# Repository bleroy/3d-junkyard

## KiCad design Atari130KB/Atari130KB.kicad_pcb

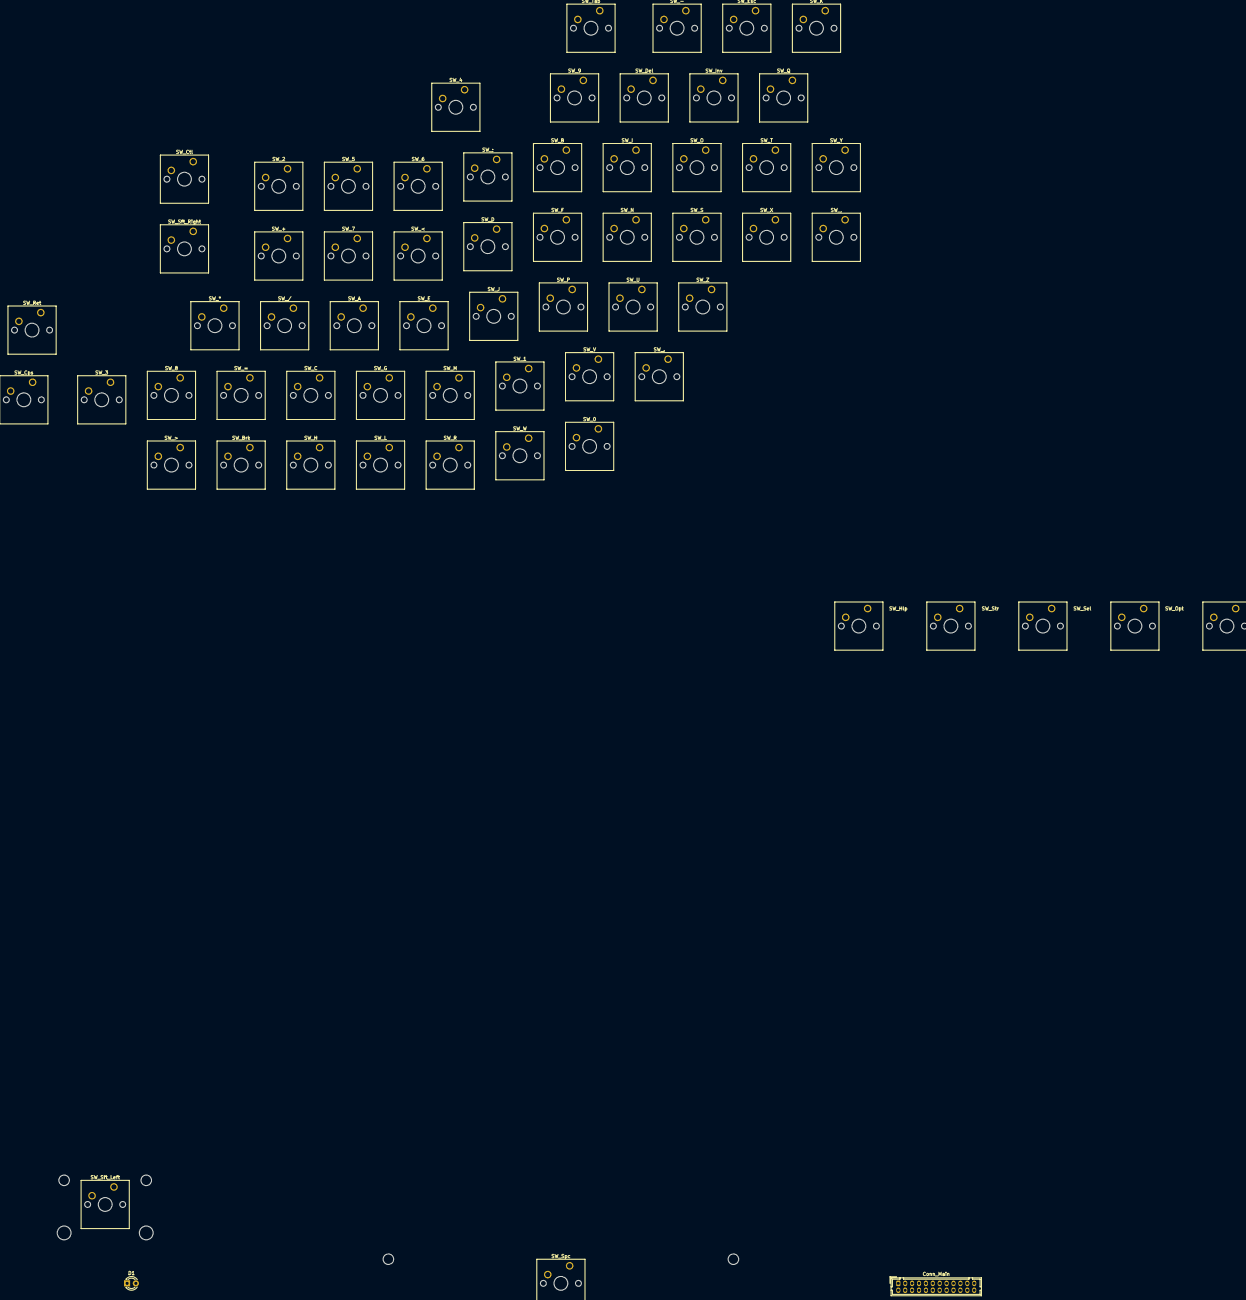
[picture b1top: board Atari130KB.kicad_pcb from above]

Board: 2 copper layers, 64 parts (0 on the bottom side), 15 nets, no tracks yet.

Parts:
Conn_Main: Conn_02x12_Counter_Clockwise_MountingPin; Hirose_DF11-24DP-2DSA_2x12_P2.00mm_Vertical
D1: LED; LED_D3.0mm
SW_0, SW_1, SW_2, SW_3, SW_4, SW_5, SW_6, SW_7, SW_8, SW_9, SW_.: SW_MEC_5G; SW_Cherry_MX_1.00u_PCB
SW_*: SW_MEC_5G; SW_Cherry_MX_1.00u_PCB
SW_+: SW_MEC_5G; SW_Cherry_MX_1.00u_PCB
SW_,: SW_MEC_5G; SW_Cherry_MX_1.00u_PCB
SW_-: SW_MEC_5G; SW_Cherry_MX_1.00u_PCB
SW_/: SW_MEC_5G; SW_Cherry_MX_1.00u_PCB
SW_;: SW_MEC_5G; SW_Cherry_MX_1.00u_PCB
SW_<: SW_MEC_5G; SW_Cherry_MX_1.00u_PCB
SW_=: SW_MEC_5G; SW_Cherry_MX_1.00u_PCB
SW_>: SW_MEC_5G; SW_Cherry_MX_1.00u_PCB
SW_A: SW_MEC_5G; SW_Cherry_MX_1.00u_PCB
SW_B: SW_MEC_5G; SW_Cherry_MX_1.00u_PCB
SW_Brk: SW_MEC_5G; SW_Cherry_MX_1.00u_PCB
SW_C: SW_MEC_5G; SW_Cherry_MX_1.00u_PCB
SW_Cps: SW_MEC_5G; SW_Cherry_MX_1.25u_PCB
SW_Ctl: SW_MEC_5G; SW_Cherry_MX_1.75u_PCB
SW_D: SW_MEC_5G; SW_Cherry_MX_1.00u_PCB
SW_Del: SW_MEC_5G; SW_Cherry_MX_1.00u_PCB
SW_E: SW_MEC_5G; SW_Cherry_MX_1.00u_PCB
SW_Esc: SW_MEC_5G; SW_Cherry_MX_1.00u_PCB
SW_F: SW_MEC_5G; SW_Cherry_MX_1.00u_PCB
SW_G: SW_MEC_5G; SW_Cherry_MX_1.00u_PCB
SW_H: SW_MEC_5G; SW_Cherry_MX_1.00u_PCB
SW_Hlp: SW_MEC_5G; SW_Cherry_MX_1.50u_Atari_Fn_PCB
SW_I: SW_MEC_5G; SW_Cherry_MX_1.00u_PCB
SW_Inv: SW_MEC_5G; SW_Cherry_MX_1.00u_PCB
SW_J: SW_MEC_5G; SW_Cherry_MX_1.00u_PCB
SW_K: SW_MEC_5G; SW_Cherry_MX_1.00u_PCB
SW_L: SW_MEC_5G; SW_Cherry_MX_1.00u_PCB
SW_M: SW_MEC_5G; SW_Cherry_MX_1.00u_PCB
SW_N: SW_MEC_5G; SW_Cherry_MX_1.00u_PCB
SW_O: SW_MEC_5G; SW_Cherry_MX_1.00u_PCB
SW_Opt: SW_MEC_5G; SW_Cherry_MX_1.50u_Atari_Fn_PCB
SW_P: SW_MEC_5G; SW_Cherry_MX_1.00u_PCB
SW_Q: SW_MEC_5G; SW_Cherry_MX_1.00u_PCB
SW_R: SW_MEC_5G; SW_Cherry_MX_1.00u_PCB
SW_Ret: SW_MEC_5G; SW_Cherry_MX_1.50u_PCB
SW_Rst: SW_MEC_5G; SW_Cherry_MX_1.50u_Atari_Fn_PCB
SW_S: SW_MEC_5G; SW_Cherry_MX_1.00u_PCB
SW_Sel: SW_MEC_5G; SW_Cherry_MX_1.50u_Atari_Fn_PCB
SW_Sft_Left: SW_MEC_5G; SW_Cherry_MX_2.25u_PCB
SW_Sft_Right: SW_MEC_5G; SW_Cherry_MX_1.75u_PCB
SW_Spc: SW_MEC_5G; SW_Cherry_MX_6.25u_PCB
SW_Str: SW_MEC_5G; SW_Cherry_MX_1.50u_Atari_Fn_PCB
SW_T: SW_MEC_5G; SW_Cherry_MX_1.00u_PCB
SW_Tab: SW_MEC_5G; SW_Cherry_MX_1.50u_PCB
SW_U: SW_MEC_5G; SW_Cherry_MX_1.00u_PCB
SW_V: SW_MEC_5G; SW_Cherry_MX_1.00u_PCB
SW_W: SW_MEC_5G; SW_Cherry_MX_1.00u_PCB
SW_X: SW_MEC_5G; SW_Cherry_MX_1.00u_PCB
SW_Y: SW_MEC_5G; SW_Cherry_MX_1.00u_PCB
SW_Z: SW_MEC_5G; SW_Cherry_MX_1.00u_PCB

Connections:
unnamed: Conn_Main.2, D1.2
unnamed: Conn_Main.3, D1.1
unnamed: Conn_Main.4, SW_H.1, SW_H.2, SW_Hlp.1, SW_Hlp.2, SW_J.1, SW_J.2, SW_Spc.1, SW_Spc.2
unnamed: Conn_Main.8, SW_5.1, SW_5.2, SW_8.1, SW_8.2, SW_B.1, SW_B.2, SW_G.1, SW_G.2, SW_I.1, SW_I.2, SW_K.1, SW_K.2, SW_M.1, SW_M.2, SW_T.1, SW_T.2
unnamed: Conn_Main.9, SW_4.1, SW_4.2, SW_9.1, SW_9.2, SW_,.1, SW_,.2, SW_F.1, SW_F.2, SW_L.1, SW_L.2, SW_O.1, SW_O.2, SW_R.1, SW_R.2, SW_V.1, SW_V.2
unnamed: Conn_Main.10, SW_0.1, SW_0.2, SW_3.1, SW_3.2, SW_..1, SW_..2, SW_;.1, SW_;.2, SW_C.1, SW_C.2, SW_D.1, SW_D.2, SW_E.1, SW_E.2, SW_P.1, SW_P.2
unnamed: Conn_Main.11, SW_2.1, SW_2.2, SW_+.1, SW_+.2, SW_-.1, SW_-.2, SW_/.1, SW_/.2, SW_<.1, SW_<.2, SW_S.1, SW_S.2, SW_W.1, SW_W.2, SW_X.1, SW_X.2
unnamed: Conn_Main.16, SW_Cps.1, SW_Cps.2, SW_Del.1, SW_Del.2, SW_Esc.1, SW_Esc.2, SW_Ret.1, SW_Ret.2, SW_Tab.1, SW_Tab.2
unnamed: Conn_Main.17, SW_1.1, SW_1.2, SW_*.1, SW_*.2, SW_=.1, SW_=.2, SW_>.1, SW_>.2, SW_A.1, SW_A.2, SW_Inv.1, SW_Inv.2, SW_Q.1, SW_Q.2, SW_Z.1, SW_Z.2
unnamed: Conn_Main.19, SW_6.1, SW_6.2, SW_7.1, SW_7.2, SW_N.1, SW_N.2, SW_U.1, SW_U.2, SW_Y.1, SW_Y.2
unnamed: Conn_Main.20, SW_Brk.1, SW_Brk.2, SW_Ctl.1, SW_Ctl.2, SW_Sft_Left.1, SW_Sft_Left.2, SW_Sft_Right.1, SW_Sft_Right.2
unnamed: Conn_Main.21, SW_Str.1, SW_Str.2
unnamed: Conn_Main.22, SW_Sel.1, SW_Sel.2
unnamed: Conn_Main.23, SW_Opt.1, SW_Opt.2
unnamed: Conn_Main.24, SW_Rst.1, SW_Rst.2

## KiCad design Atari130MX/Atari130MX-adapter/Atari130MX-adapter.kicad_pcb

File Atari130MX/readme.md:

This page moved [here](../DecentXE/readme.md).

All old versions of the files have been kept in place in order to avoid breaking links, but the newer versions in the DecentXE directory should now be used.

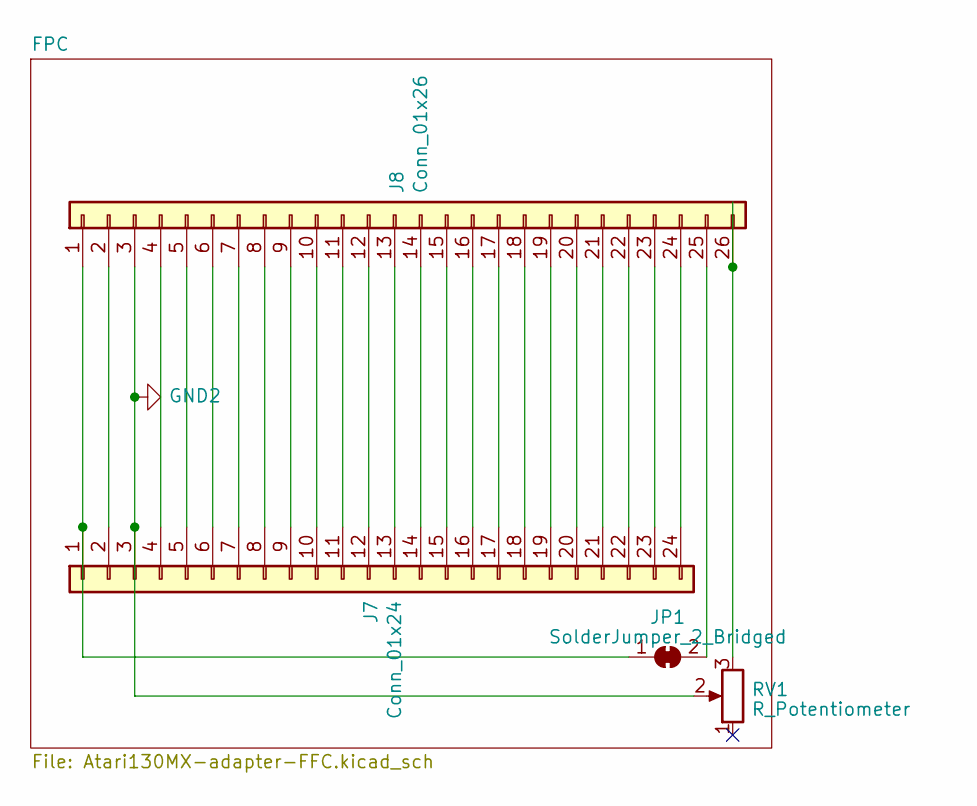
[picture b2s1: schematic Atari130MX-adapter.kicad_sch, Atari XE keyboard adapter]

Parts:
J7: Conn_01x24; 1x24_P1.27mm_Edge_Back
J8: Conn_01x26; Molex_200528-0260_1x26-1MP_P1.00mm_Horizontal
JP1: SolderJumper_2_Bridged; SolderJumper-2_P1.3mm_Bridged_RoundedPad1.0x1.5mm
RV1: R_Potentiometer; Potentiometer_CUI-PTN06-D02CB20

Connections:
GND2: J7.3, J8.3, RV1.2
unnamed: J7.1, J8.1, JP1.1 (A)
unnamed: J7.2, J8.2
unnamed: J7.4, J8.4
unnamed: J7.5, J8.5
unnamed: J7.6, J8.6
unnamed: J7.7, J8.7
unnamed: J7.8, J8.8
unnamed: J7.9, J8.9
unnamed: J7.10, J8.10
unnamed: J7.11, J8.11
unnamed: J7.12, J8.12
unnamed: J7.13, J8.13
unnamed: J7.14, J8.14
unnamed: J7.15, J8.15
unnamed: J7.16, J8.16
unnamed: J7.17, J8.17
unnamed: J7.18, J8.18
unnamed: J7.19, J8.19
unnamed: J7.20, J8.20
unnamed: J7.21, J8.21
unnamed: J7.22, J8.22
unnamed: J7.23, J8.23
unnamed: J7.24, J8.24
unnamed: J8.25, JP1.2 (B)
unnamed: J8.26, RV1.3

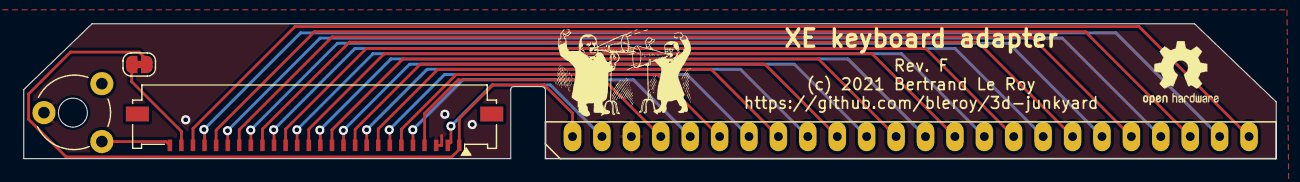
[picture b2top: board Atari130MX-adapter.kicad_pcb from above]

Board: 2 copper layers, 108.1 x 11.6 mm, 4 parts (0 on the bottom side), 26 nets.

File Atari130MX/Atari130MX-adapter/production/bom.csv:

Designator,Footprint,Quantity,Value,LCSC Part #
J1,FPC 1x24 P2.54mm Edge,1,Conn_01x24,
J2,FPC Molex 1x26 P1mm Edge,1,Conn_01x26,

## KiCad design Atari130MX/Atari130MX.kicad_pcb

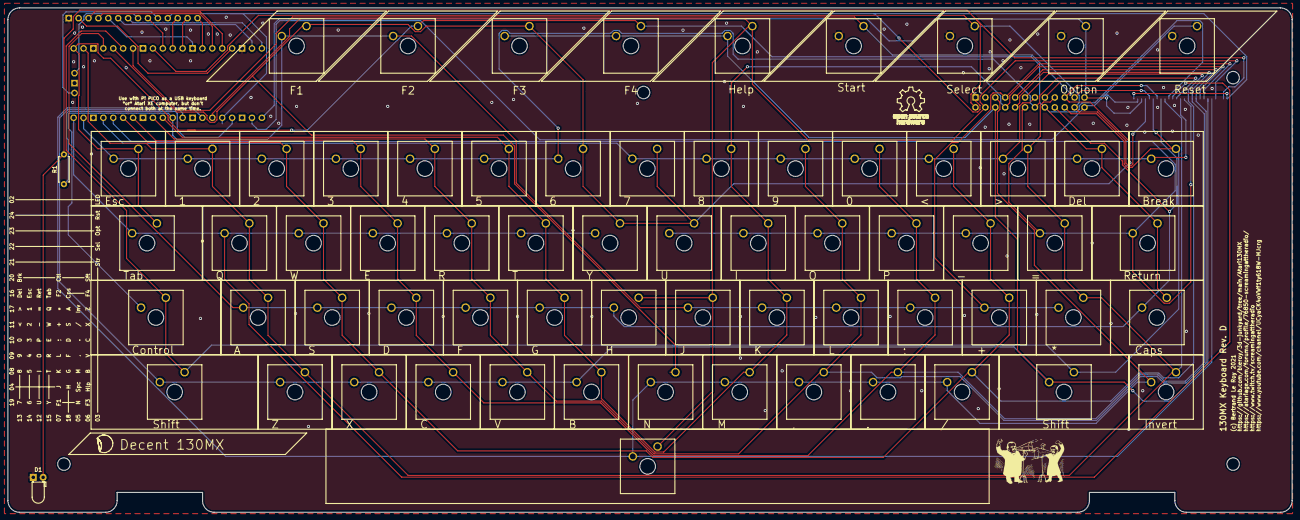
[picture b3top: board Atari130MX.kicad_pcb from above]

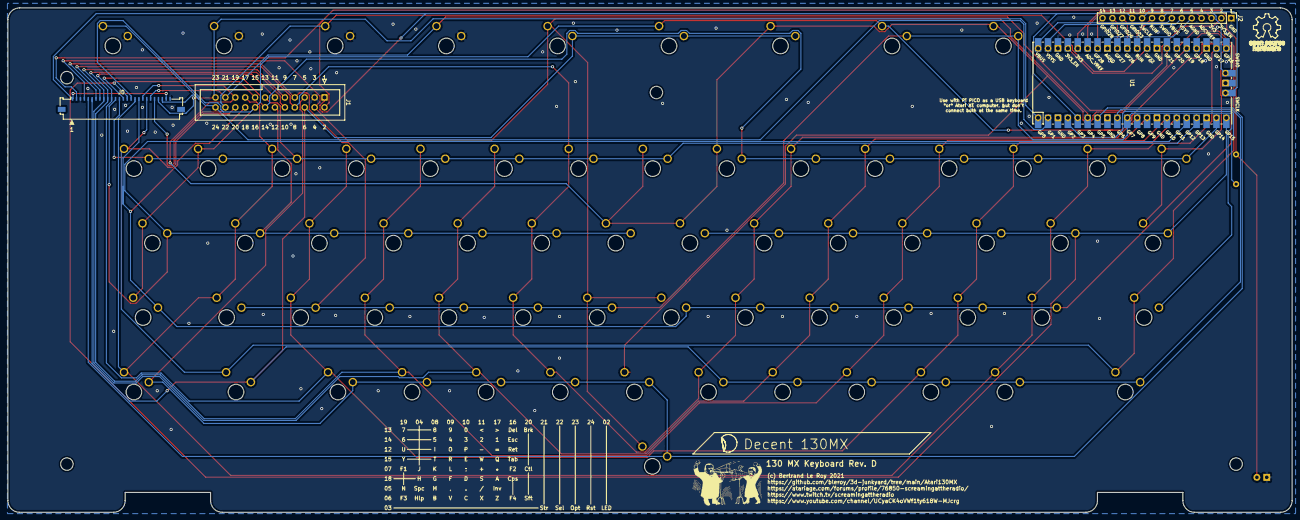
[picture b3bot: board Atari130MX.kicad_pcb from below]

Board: 2 copper layers, 329.2 x 129.3 mm, 76 parts (4 on the bottom side), 37 nets.

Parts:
D1: LED; LED_D3.0mm_Horizontal_O1.27mm_Z2.0mm
J0: Conn_01x26; Molex_200528-0260_1x26-1MP_P1.00mm_Horizontal
J1: Conn_02x12_Odd_Even; IDC-Header_2x12_P2.54mm_Vertical
J2: Conn_01x14; PinHeader_1x14_P2.54mm_Vertical
R1: R100; R_Axial_DIN0207_L6.3mm_D2.5mm_P7.62mm_Horizontal
REF0, REF01, REF02, REF03: MountingHole_3.2mm_M3
SW0, SW1, SW2, SW3, SW4, SW5, SW6, SW7, SW8, SW9: SW_Push_45deg; SW_Kailh_1.00u_PCB
SWA1: SW_Push_45deg; SW_Kailh_1.00u_PCB
SWB1: SW_Push_45deg; SW_Kailh_1.00u_PCB
SWBrk1: SW_Push_45deg; SW_Kailh_1.00u_PCB
SWC1: SW_Push_45deg; SW_Kailh_1.00u_PCB
SWComma1: SW_Push_45deg; SW_Kailh_1.00u_PCB
SWCps1: SW_Push_45deg; SW_Kailh_1.25u_PCB
SWCtl1: SW_Push_45deg; SW_Kailh_1.75u_PCB
SWD1: SW_Push_45deg; SW_Kailh_1.00u_PCB
SWDash1: SW_Push_45deg; SW_Kailh_1.00u_PCB
SWDel1: SW_Push_45deg; SW_Kailh_1.00u_PCB
SWE1: SW_Push_45deg; SW_Kailh_1.00u_PCB
SWEqual1: SW_Push_45deg; SW_Kailh_1.00u_PCB
SWEsc1: SW_Push_45deg; SW_Kailh_1.00u_PCB
SWF1: SW_Push_45deg; SW_Kailh_1.00u_PCB
SWFn1, SWFn2, SWFn3, SWFn4: SW_Push_45deg; SW_Kailh_1.50u_Atari_Fn_PCB
SWG1: SW_Push_45deg; SW_Kailh_1.00u_PCB
SWGT1: SW_Push_45deg; SW_Kailh_1.00u_PCB
SWH1: SW_Push_45deg; SW_Kailh_1.00u_PCB
SWHlp1: SW_Push_45deg; SW_Kailh_1.50u_Atari_Fn_PCB
SWI1: SW_Push_45deg; SW_Kailh_1.00u_PCB
SWInv1: SW_Push_45deg; SW_Kailh_1.00u_PCB
SWJ1: SW_Push_45deg; SW_Kailh_1.00u_PCB
SWK1: SW_Push_45deg; SW_Kailh_1.00u_PCB
SWL1: SW_Push_45deg; SW_Kailh_1.00u_PCB
SWLT1: SW_Push_45deg; SW_Kailh_1.00u_PCB
SWLeftSft1: SW_Push_45deg; SW_Kailh_2.25u_PCB
SWM1: SW_Push_45deg; SW_Kailh_1.00u_PCB
SWN1: SW_Push_45deg; SW_Kailh_1.00u_PCB
SWO1: SW_Push_45deg; SW_Kailh_1.00u_PCB
SWOption1: SW_Push_45deg; SW_Kailh_1.50u_Atari_Fn_PCB
SWP1: SW_Push_45deg; SW_Kailh_1.00u_PCB
SWPeriod1: SW_Push_45deg; SW_Kailh_1.00u_PCB
SWPlus1: SW_Push_45deg; SW_Kailh_1.00u_PCB
SWQ1: SW_Push_45deg; SW_Kailh_1.00u_PCB
SWR1: SW_Push_45deg; SW_Kailh_1.00u_PCB
SWReset1: SW_Push_45deg; SW_Kailh_1.50u_Atari_Fn_PCB
SWRet1: SW_Push_45deg; SW_Kailh_1.50u_PCB
SWRightSft1: SW_Push_45deg; SW_Kailh_1.75u_PCB
SWS1: SW_Push_45deg; SW_Kailh_1.00u_PCB
SWSelect1: SW_Push_45deg; SW_Kailh_1.50u_Atari_Fn_PCB
SWSemi1: SW_Push_45deg; SW_Kailh_1.00u_PCB
SWSlash1: SW_Push_45deg; SW_Kailh_1.00u_PCB
SWSpc1: SW_Push_45deg; SW_Kailh_Atari_Space
SWStar1: SW_Push_45deg; SW_Kailh_1.00u_PCB
SWStart1: SW_Push_45deg; SW_Kailh_1.50u_Atari_Fn_PCB
SWT1: SW_Push_45deg; SW_Kailh_1.00u_PCB
SWTab1: SW_Push_45deg; SW_Kailh_1.50u_PCB
SWU1: SW_Push_45deg; SW_Kailh_1.00u_PCB
SWV1: SW_Push_45deg; SW_Kailh_1.00u_PCB
SWW1: SW_Push_45deg; SW_Kailh_1.00u_PCB
SWX1: SW_Push_45deg; SW_Kailh_1.00u_PCB
SWY1: SW_Push_45deg; SW_Kailh_1.00u_PCB
SWZ1: SW_Push_45deg; SW_Kailh_1.00u_PCB
U1: Pico; RPi_Pico_SMD_TH

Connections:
GND: D1.1, J0.3, J0.26, J1.3, J2.1, SWOption1.2, SWReset1.2, SWSelect1.2, SWStart1.2, U1.38
unnamed: D1.2, J0.2, J1.2, R1.2
unnamed: J0.1, J0.25, J1.1, J2.11, U1.5
unnamed: J0.4, J1.4, SWH1.1, SWHlp1.1, SWJ1.1, SWSpc1.1, U1.6
unnamed: J0.5, J1.5, SWComma1.2, SWInv1.2, SWM1.2, SWN1.2, SWPeriod1.2, SWSlash1.2, SWSpc1.2, U1.7
unnamed: J0.6, J1.6, SWB1.2, SWC1.2, SWFn3.2, SWFn4.2, SWHlp1.2, SWLeftSft1.2, SWRightSft1.2, SWV1.2, SWX1.2, SWZ1.2, U1.9
unnamed: J0.7, J1.7, SWCtl1.2, SWFn1.2, SWFn2.2, SWJ1.2, SWK1.2, SWL1.2, SWPlus1.2, SWSemi1.2, SWStar1.2, U1.10
unnamed: J0.8, J1.8, SW5.1, SW8.1, SWB1.1, SWG1.1, SWI1.1, SWK1.1, SWM1.1, SWT1.1, U1.11
unnamed: J0.9, J1.9, SW4.1, SW9.1, SWComma1.1, SWF1.1, SWL1.1, SWO1.1, SWR1.1, SWV1.1, U1.12
unnamed: J0.10, J1.10, SW0.1, SW3.1, SWC1.1, SWD1.1, SWE1.1, SWP1.1, SWPeriod1.1, SWSemi1.1, U1.14
unnamed: J0.11, J1.11, SW2.1, SWDash1.1, SWLT1.1, SWPlus1.1, SWS1.1, SWSlash1.1, SWW1.1, SWX1.1, U1.15
unnamed: J0.12, J1.12, SWDash1.2, SWEqual1.2, SWI1.2, SWO1.2, SWP1.2, SWRet1.2, SWU1.2, U1.16
unnamed: J0.13, J1.13, SW0.2, SW7.2, SW8.2, SW9.2, SWBrk1.2, SWDel1.2, SWGT1.2, SWLT1.2, U1.17
unnamed: J0.14, J1.14, SW1.2, SW2.2, SW3.2, SW4.2, SW5.2, SW6.2, SWEsc1.2, U1.19
unnamed: J0.15, J1.15, SWE1.2, SWQ1.2, SWR1.2, SWT1.2, SWTab1.2, SWW1.2, SWY1.2, U1.20
unnamed: J0.16, J1.16, SWCps1.1, SWDel1.1, SWEsc1.1, SWFn2.1, SWFn4.1, SWRet1.1, SWTab1.1, U1.21
unnamed: J0.17, J1.17, SW1.1, SWA1.1, SWEqual1.1, SWGT1.1, SWInv1.1, SWQ1.1, SWStar1.1, SWZ1.1, U1.22
unnamed: J0.18, J1.18, SWA1.2, SWCps1.2, SWD1.2, SWF1.2, SWG1.2, SWH1.2, SWS1.2, U1.24
unnamed: J0.19, J1.19, SW6.1, SW7.1, SWFn1.1, SWFn3.1, SWN1.1, SWU1.1, SWY1.1, U1.25
unnamed: J0.20, J1.20, SWBrk1.1, SWCtl1.1, SWLeftSft1.1, SWRightSft1.1, U1.26
unnamed: J0.21, J1.21, SWStart1.1, U1.27
unnamed: J0.22, J1.22, SWSelect1.1, U1.29
unnamed: J0.23, J1.23, SWOption1.1, U1.1
unnamed: J0.24, J1.24, SWReset1.1, U1.2
unnamed: J2.2, U1.37
unnamed: J2.3, U1.36
unnamed: J2.4, U1.35
unnamed: J2.5, U1.33
unnamed: J2.6, U1.39
unnamed: J2.7, U1.40
unnamed: J2.8, U1.43
unnamed: J2.9, U1.30
unnamed: J2.10, U1.41
unnamed: J2.12, U1.31
unnamed: J2.13, U1.32
unnamed: J2.14, U1.34
unnamed: R1.1, U1.4

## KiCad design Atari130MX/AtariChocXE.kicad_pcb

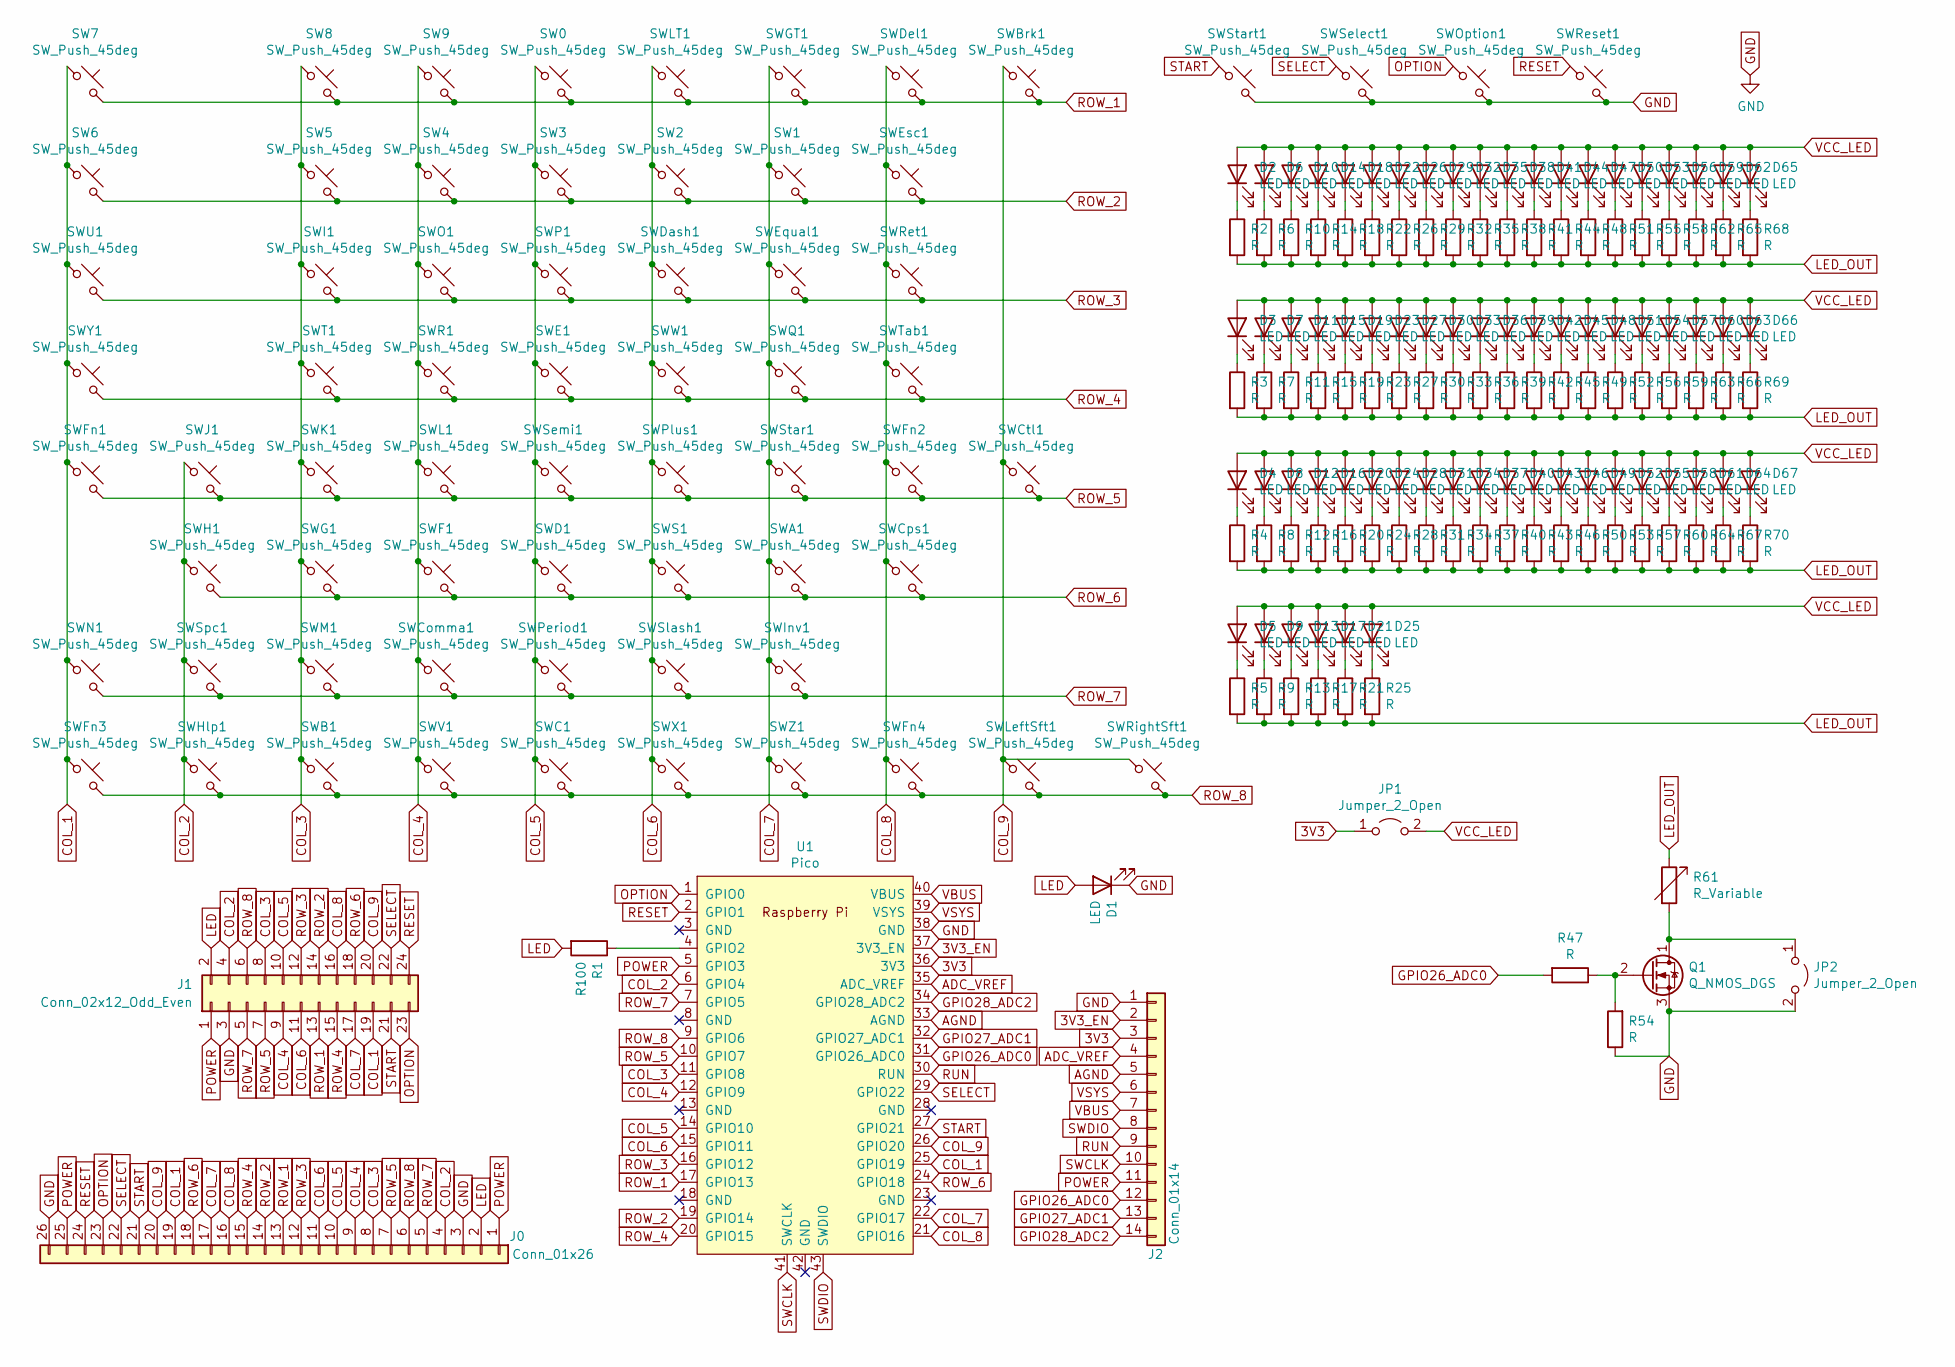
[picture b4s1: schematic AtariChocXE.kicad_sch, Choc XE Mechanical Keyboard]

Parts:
D1: LED; LED_D3.0mm_Horizontal_O1.27mm_Z2.0mm
D2, D3, D4, D5, D6, D7, D8, D9, D10, D11, D12, D13, D14, D15, D16, D17, D18, D19, D20, D21, D22, D23, D24, D25, D26, D27, D28, D29, D30, D31, D32, D33, D34, D35, D36, D37, D38, D39, D40, D41, D42, D43, D44, D45, D46, D47, D48, D49, D50, D51, D52, D53, D54, D55, D56, D57, D58, D59, D60, D61, D62, D63, D64, D65, D66, D67: LED; LED_KBD_1.8mm
J0: Conn_01x26; Molex_200528-0260_1x26-1MP_P1.00mm_Horizontal
J1: Conn_02x12_Odd_Even; IDC-Header_2x12_P2.54mm_Vertical
J2: Conn_01x14; PinHeader_1x14_P2.54mm_Vertical
JP1, JP2: Jumper_2_Open; PinHeader_1x02_P2.54mm_Vertical
Q1: Q_NMOS_DGS; TO-92
R1: R100; R_Axial_DIN0207_L6.3mm_D2.5mm_P7.62mm_Horizontal
R2, R3, R4, R5, R6, R7, R8, R9, R10, R11, R12, R13, R14, R15, R16, R17, R18, R19, R20, R21, R22, R23, R24, R25, R26, R27, R28, R29, R30, R31, R32, R33, R34, R35, R36, R37, R38, R39, R40, R41, R42, R43, R44, R45, R46, R47, R48, R49, R50, R51, R52, R53, R54, R55, R56, R57, R58, R59, R60, R62, R63, R64, R65, R66, R67, R68, R69, R70: R; R_Axial_DIN0207_L6.3mm_D2.5mm_P7.62mm_Horizontal
R61: R_Variable; Potentiometer_Piher_PT-10-V10_Vertical
SW0, SW1, SW2, SW3, SW4, SW5, SW6, SW7, SW8, SW9: SW_Push_45deg; SW_Kailh_Choc_1.00u_PCB
SWA1: SW_Push_45deg; SW_Kailh_Choc_1.00u_PCB
SWB1: SW_Push_45deg; SW_Kailh_Choc_1.00u_PCB
SWBrk1: SW_Push_45deg; SW_Kailh_Choc_1.00u_PCB
SWC1: SW_Push_45deg; SW_Kailh_Choc_1.00u_PCB
SWComma1: SW_Push_45deg; SW_Kailh_Choc_1.00u_PCB
SWCps1: SW_Push_45deg; SW_Kailh_Choc_1.00u_PCB
SWCtl1: SW_Push_45deg; SW_Kailh_Choc_1.00u_PCB
SWD1: SW_Push_45deg; SW_Kailh_Choc_1.00u_PCB
SWDash1: SW_Push_45deg; SW_Kailh_Choc_1.00u_PCB
SWDel1: SW_Push_45deg; SW_Kailh_Choc_1.00u_PCB
SWE1: SW_Push_45deg; SW_Kailh_Choc_1.00u_PCB
SWEqual1: SW_Push_45deg; SW_Kailh_Choc_1.00u_PCB
SWEsc1: SW_Push_45deg; SW_Kailh_Choc_1.00u_PCB
SWF1: SW_Push_45deg; SW_Kailh_Choc_1.00u_PCB
SWFn1, SWFn2, SWFn3, SWFn4: SW_Push_45deg; SW_Kailh_Choc_1.50u_Atari_Fn_PCB
SWG1: SW_Push_45deg; SW_Kailh_Choc_1.00u_PCB
SWGT1: SW_Push_45deg; SW_Kailh_Choc_1.00u_PCB
SWH1: SW_Push_45deg; SW_Kailh_Choc_1.00u_PCB
SWHlp1: SW_Push_45deg; SW_Kailh_Choc_1.50u_Atari_Fn_PCB
SWI1: SW_Push_45deg; SW_Kailh_Choc_1.00u_PCB
SWInv1: SW_Push_45deg; SW_Kailh_Choc_1.00u_PCB
SWJ1: SW_Push_45deg; SW_Kailh_Choc_1.00u_PCB
SWK1: SW_Push_45deg; SW_Kailh_Choc_1.00u_PCB
SWL1: SW_Push_45deg; SW_Kailh_Choc_1.00u_PCB
SWLT1: SW_Push_45deg; SW_Kailh_Choc_1.00u_PCB
SWLeftSft1: SW_Push_45deg; SW_Kailh_Choc_2.25u_PCB
SWM1: SW_Push_45deg; SW_Kailh_Choc_1.00u_PCB
SWN1: SW_Push_45deg; SW_Kailh_Choc_1.00u_PCB
SWO1: SW_Push_45deg; SW_Kailh_Choc_1.00u_PCB
SWOption1: SW_Push_45deg; SW_Kailh_Choc_1.50u_Atari_Fn_PCB
SWP1: SW_Push_45deg; SW_Kailh_Choc_1.00u_PCB
SWPeriod1: SW_Push_45deg; SW_Kailh_Choc_1.00u_PCB
SWPlus1: SW_Push_45deg; SW_Kailh_Choc_1.00u_PCB
SWQ1: SW_Push_45deg; SW_Kailh_Choc_1.00u_PCB
SWR1: SW_Push_45deg; SW_Kailh_Choc_1.00u_PCB
SWReset1: SW_Push_45deg; SW_Kailh_Choc_1.50u_Atari_Fn_PCB
SWRet1: SW_Push_45deg; SW_Kailh_Choc_1.50u_PCB
SWRightSft1: SW_Push_45deg; SW_Kailh_Choc_1.75u_PCB
SWS1: SW_Push_45deg; SW_Kailh_Choc_1.00u_PCB
SWSelect1: SW_Push_45deg; SW_Kailh_Choc_1.50u_Atari_Fn_PCB
SWSemi1: SW_Push_45deg; SW_Kailh_Choc_1.00u_PCB
SWSlash1: SW_Push_45deg; SW_Kailh_Choc_1.00u_PCB
SWSpc1: SW_Push_45deg; SW_Kailh_Choc_Atari_Space
SWStar1: SW_Push_45deg; SW_Kailh_Choc_1.00u_PCB
SWStart1: SW_Push_45deg; SW_Kailh_Choc_1.50u_Atari_Fn_PCB
SWT1: SW_Push_45deg; SW_Kailh_Choc_1.00u_PCB
SWTab1: SW_Push_45deg; SW_Kailh_Choc_1.50u_PCB
SWU1: SW_Push_45deg; SW_Kailh_Choc_1.00u_PCB
SWV1: SW_Push_45deg; SW_Kailh_Choc_1.00u_PCB
SWW1: SW_Push_45deg; SW_Kailh_Choc_1.00u_PCB
SWX1: SW_Push_45deg; SW_Kailh_Choc_1.00u_PCB
SWY1: SW_Push_45deg; SW_Kailh_Choc_1.00u_PCB
SWZ1: SW_Push_45deg; SW_Kailh_Choc_1.00u_PCB
U1: Pico; RPi_Pico_SMD_TH

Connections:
3V3: J2.3, JP1.1 (A), U1.36 (3V3)
3V3_EN: J2.2, U1.37 (3V3_EN)
ADC_VREF: J2.4, U1.35 (ADC_VREF)
AGND: J2.5, U1.33 (AGND)
COL_1: J0.19, J1.19, SW6.1, SW7.1, SWFn1.1, SWFn3.1, SWN1.1, SWU1.1, SWY1.1, U1.25 (GPIO19)
COL_2: J0.4, J1.4, SWH1.1, SWHlp1.1, SWJ1.1, SWSpc1.1, U1.6 (GPIO4)
COL_3: J0.8, J1.8, SW5.1, SW8.1, SWB1.1, SWG1.1, SWI1.1, SWK1.1, SWM1.1, SWT1.1, U1.11 (GPIO8)
COL_4: J0.9, J1.9, SW4.1, SW9.1, SWComma1.1, SWF1.1, SWL1.1, SWO1.1, SWR1.1, SWV1.1, U1.12 (GPIO9)
COL_5: J0.10, J1.10, SW0.1, SW3.1, SWC1.1, SWD1.1, SWE1.1, SWP1.1, SWPeriod1.1, SWSemi1.1, U1.14 (GPIO10)
COL_6: J0.11, J1.11, SW2.1, SWDash1.1, SWLT1.1, SWPlus1.1, SWS1.1, SWSlash1.1, SWW1.1, SWX1.1, U1.15 (GPIO11)
COL_7: J0.17, J1.17, SW1.1, SWA1.1, SWEqual1.1, SWGT1.1, SWInv1.1, SWQ1.1, SWStar1.1, SWZ1.1, U1.22 (GPIO17)
COL_8: J0.16, J1.16, SWCps1.1, SWDel1.1, SWEsc1.1, SWFn2.1, SWFn4.1, SWRet1.1, SWTab1.1, U1.21 (GPIO16)
COL_9: J0.20, J1.20, SWBrk1.1, SWCtl1.1, SWLeftSft1.1, SWRightSft1.1, U1.26 (GPIO20)
GND: D1.1 (K), J0.3, J0.26, J1.3, J2.1, JP2.2 (B), Q1.3 (S), R54.1, SWOption1.2, SWReset1.2, SWSelect1.2, SWStart1.2, U1.38 (GND)
GPIO26_ADC0: J2.12, R47.2, U1.31 (GPIO26_ADC0)
GPIO27_ADC1: J2.13, U1.32 (GPIO27_ADC1)
GPIO28_ADC2: J2.14, U1.34 (GPIO28_ADC2)
LED: D1.2 (A), J0.2, J1.2, R1.2
LED_OUT: R2.2, R3.2, R4.2, R5.2, R6.2, R7.2, R8.2, R9.2, R10.2, R11.2, R12.2, R13.2, R14.2, R15.2, R16.2, R17.2, R18.2, R19.2, R20.2, R21.2, R22.2, R23.2, R24.2, R25.2, R26.2, R27.2, R28.2, R29.2, R30.2, R31.2, R32.2, R33.2, R34.2, R35.2, R36.2, R37.2, R38.2, R39.2, R40.2, R41.2, R42.2, R43.2, R44.2, R45.2, R46.2, R48.2, R49.2, R50.2, R51.2, R52.2, R53.2, R55.2, R56.2, R57.2, R58.2, R59.2, R60.2, R61.1, R62.2, R63.2, R64.2, R65.2, R66.2, R67.2, R68.2, R69.2, R70.2
unnamed: D2.1 (K), R2.1
unnamed: D3.1 (K), R3.1
unnamed: D4.1 (K), R4.1
unnamed: D5.1 (K), R5.1
unnamed: D6.1 (K), R6.1
unnamed: D7.1 (K), R7.1
unnamed: D8.1 (K), R8.1
unnamed: D9.1 (K), R9.1
unnamed: D10.1 (K), R10.1
unnamed: D11.1 (K), R11.1
unnamed: D12.1 (K), R12.1
unnamed: D13.1 (K), R13.1
unnamed: D14.1 (K), R14.1
unnamed: D15.1 (K), R15.1
unnamed: D16.1 (K), R16.1
unnamed: D17.1 (K), R17.1
unnamed: D18.1 (K), R18.1
unnamed: D19.1 (K), R19.1
unnamed: D20.1 (K), R20.1
unnamed: D21.1 (K), R21.1
unnamed: D22.1 (K), R22.1
unnamed: D23.1 (K), R23.1
unnamed: D24.1 (K), R24.1
unnamed: D25.1 (K), R25.1
unnamed: D26.1 (K), R26.1
unnamed: D27.1 (K), R27.1
unnamed: D28.1 (K), R28.1
unnamed: D29.1 (K), R29.1
unnamed: D30.1 (K), R30.1
unnamed: D31.1 (K), R31.1
unnamed: D32.1 (K), R32.1
unnamed: D33.1 (K), R33.1
unnamed: D34.1 (K), R34.1
unnamed: D35.1 (K), R35.1
unnamed: D36.1 (K), R36.1
unnamed: D37.1 (K), R37.1
unnamed: D38.1 (K), R38.1
unnamed: D39.1 (K), R39.1
unnamed: D40.1 (K), R40.1
unnamed: D41.1 (K), R41.1
unnamed: D42.1 (K), R42.1
unnamed: D43.1 (K), R43.1
unnamed: D44.1 (K), R44.1
unnamed: D45.1 (K), R45.1
unnamed: D46.1 (K), R46.1
unnamed: D47.1 (K), R48.1
unnamed: D48.1 (K), R49.1
unnamed: D49.1 (K), R50.1
unnamed: D50.1 (K), R51.1
unnamed: D51.1 (K), R52.1
unnamed: D52.1 (K), R53.1
unnamed: D53.1 (K), R55.1
unnamed: D54.1 (K), R56.1
unnamed: D55.1 (K), R57.1
unnamed: D56.1 (K), R58.1
unnamed: D57.1 (K), R59.1
unnamed: D58.1 (K), R60.1
unnamed: D59.1 (K), R62.1
unnamed: D60.1 (K), R63.1
unnamed: D61.1 (K), R64.1
unnamed: D62.1 (K), R65.1
unnamed: D63.1 (K), R66.1
unnamed: D64.1 (K), R67.1
unnamed: D65.1 (K), R68.1
unnamed: D66.1 (K), R69.1
unnamed: D67.1 (K), R70.1
unnamed: JP2.1 (A), Q1.1 (D), R61.2
unnamed: Q1.2 (G), R47.1, R54.2
unnamed: R1.1, U1.4 (GPIO2)
OPTION: J0.23, J1.23, SWOption1.1, U1.1 (GPIO0)
POWER: J0.1, J0.25, J1.1, J2.11, U1.5 (GPIO3)
RESET: J0.24, J1.24, SWReset1.1, U1.2 (GPIO1)
ROW_1: J0.13, J1.13, SW0.2, SW7.2, SW8.2, SW9.2, SWBrk1.2, SWDel1.2, SWGT1.2, SWLT1.2, U1.17 (GPIO13)
ROW_2: J0.14, J1.14, SW1.2, SW2.2, SW3.2, SW4.2, SW5.2, SW6.2, SWEsc1.2, U1.19 (GPIO14)
ROW_3: J0.12, J1.12, SWDash1.2, SWEqual1.2, SWI1.2, SWO1.2, SWP1.2, SWRet1.2, SWU1.2, U1.16 (GPIO12)
ROW_4: J0.15, J1.15, SWE1.2, SWQ1.2, SWR1.2, SWT1.2, SWTab1.2, SWW1.2, SWY1.2, U1.20 (GPIO15)
ROW_5: J0.7, J1.7, SWCtl1.2, SWFn1.2, SWFn2.2, SWJ1.2, SWK1.2, SWL1.2, SWPlus1.2, SWSemi1.2, SWStar1.2, U1.10 (GPIO7)
ROW_6: J0.18, J1.18, SWA1.2, SWCps1.2, SWD1.2, SWF1.2, SWG1.2, SWH1.2, SWS1.2, U1.24 (GPIO18)
ROW_7: J0.5, J1.5, SWComma1.2, SWInv1.2, SWM1.2, SWN1.2, SWPeriod1.2, SWSlash1.2, SWSpc1.2, U1.7 (GPIO5)
ROW_8: J0.6, J1.6, SWB1.2, SWC1.2, SWFn3.2, SWFn4.2, SWHlp1.2, SWLeftSft1.2, SWRightSft1.2, SWV1.2, SWX1.2, SWZ1.2, U1.9 (GPIO6)
RUN: J2.9, U1.30 (RUN)
SELECT: J0.22, J1.22, SWSelect1.1, U1.29 (GPIO22)
START: J0.21, J1.21, SWStart1.1, U1.27 (GPIO21)
SWCLK: J2.10, U1.41 (SWCLK)
SWDIO: J2.8, U1.43 (SWDIO)
VBUS: J2.7, U1.40 (VBUS)
VCC_LED: D2.2 (A), D3.2 (A), D4.2 (A), D5.2 (A), D6.2 (A), D7.2 (A), D8.2 (A), D9.2 (A), D10.2 (A), D11.2 (A), D12.2 (A), D13.2 (A), D14.2 (A), D15.2 (A), D16.2 (A), D17.2 (A), D18.2 (A), D19.2 (A), D20.2 (A), D21.2 (A), D22.2 (A), D23.2 (A), D24.2 (A), D25.2 (A), D26.2 (A), D27.2 (A), D28.2 (A), D29.2 (A), D30.2 (A), D31.2 (A), D32.2 (A), D33.2 (A), D34.2 (A), D35.2 (A), D36.2 (A), D37.2 (A), D38.2 (A), D39.2 (A), D40.2 (A), D41.2 (A), D42.2 (A), D43.2 (A), D44.2 (A), D45.2 (A), D46.2 (A), D47.2 (A), D48.2 (A), D49.2 (A), D50.2 (A), D51.2 (A), D52.2 (A), D53.2 (A), D54.2 (A), D55.2 (A), D56.2 (A), D57.2 (A), D58.2 (A), D59.2 (A), D60.2 (A), D61.2 (A), D62.2 (A), D63.2 (A), D64.2 (A), D65.2 (A), D66.2 (A), D67.2 (A), JP1.2 (B)
VSYS: J2.6, U1.39 (VSYS)

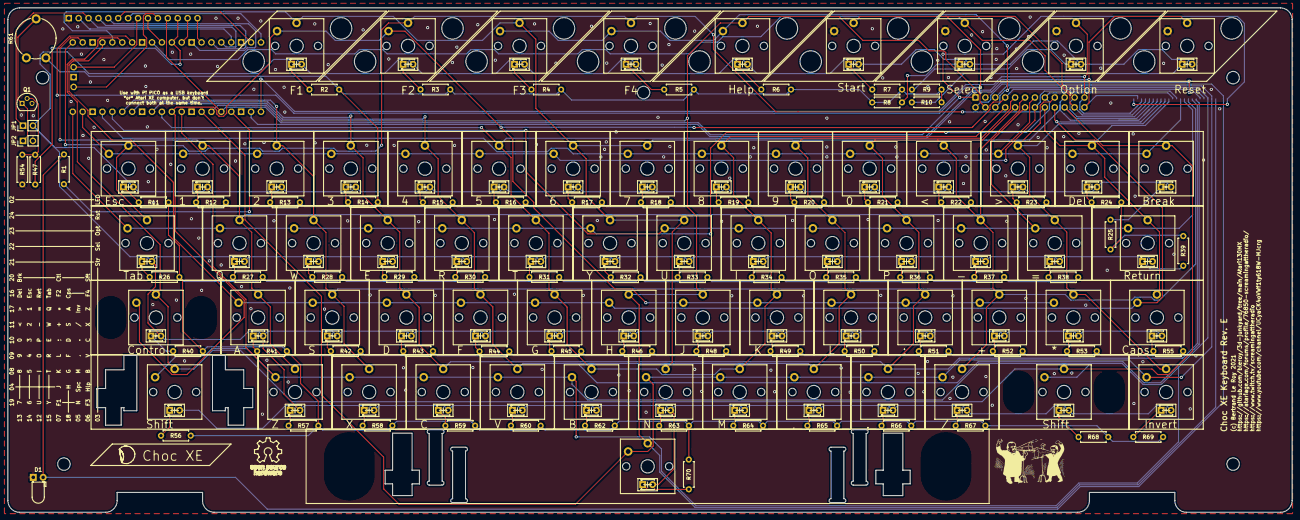
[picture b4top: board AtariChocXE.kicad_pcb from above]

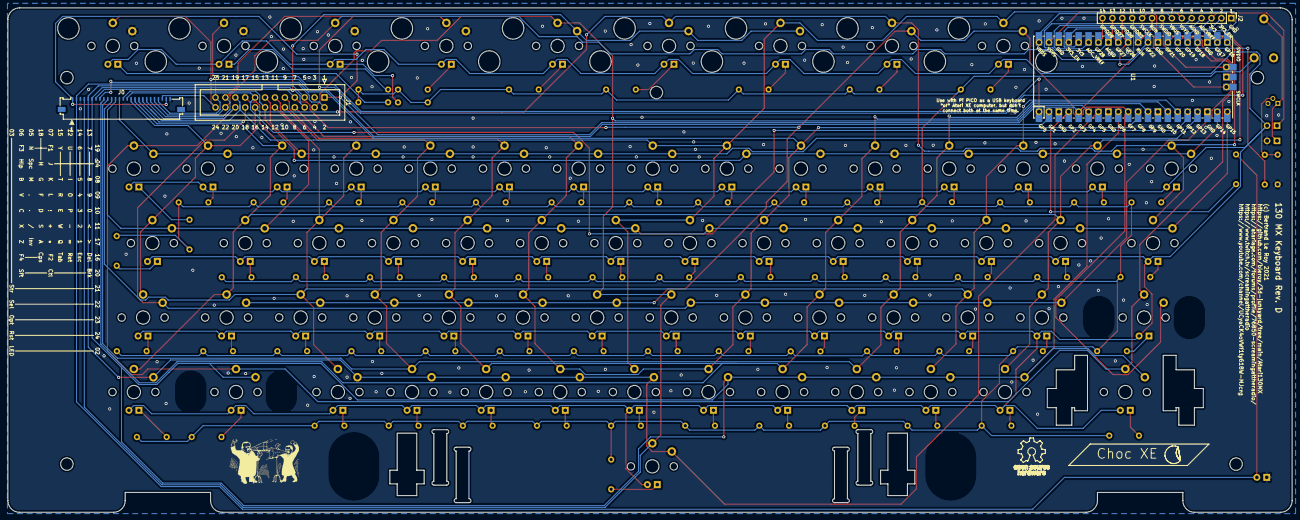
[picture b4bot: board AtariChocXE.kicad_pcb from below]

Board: 2 copper layers, 329.2 x 129.3 mm, 215 parts (4 on the bottom side), 107 nets.

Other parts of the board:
REF0, REF01, REF02, REF03, REF03#2: MountingHole_3.2mm_M3

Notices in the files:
Atari130MX/Atari130MX-adapter/Atari130MX-adapter.kicad_pcb:
(c) 2021 Bertrand Le Roy
